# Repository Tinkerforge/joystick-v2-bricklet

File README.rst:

Joystick Bricklet 2.0
=====================

This repository contains the firmware source code and the hardware design
files. The documentation generator configs can be found at
https://github.com/Tinkerforge/generators

Repository Content
------------------

software/:
 * examples/: Examples for all supported languages
 * build/: Compiled files
 * src/: Source code of firmware
 * Makefile: Makefile to build project

hardware/:
 * Contains KiCad project files and additionally schematics as PDF

datasheets/:
 * Contains datasheets for sensors and complex ICs that are used

Hardware
--------

The hardware is designed with the open source EDA Suite KiCad
(http://www.kicad.org). Before you are able to open the files,
you have to install the Tinkerforge kicad-libraries
(https://github.com/Tinkerforge/kicad-libraries). You can either clone
them directly in hardware/ or clone them in a separate folder and
symlink them into hardware/
(ln -s kicad_path/kicad-libraries project_path/hardware). After that you
can open the .pro file in hardware/ with KiCad and from there view and
modify the schematics and the PCB layout.

Software
--------

If you want to do your own Brick/Bricklet firmware development we highly
recommend that you use our build environment setup script and read the
tutorial (https://www.tinkerforge.com/en/doc/Tutorials/Tutorial_Build_Environment/Tutorial.html).

To compile the C code we recommend you to install the newest GNU Arm Embedded
Toolchain (https://launchpad.net/gcc-arm-embedded/+download).
You also need to install bricklib2 (https://github.com/Tinkerforge/bricklib2).

You can either clone it directly in software/src/ or clone it in a
separate folder and symlink it into software/src/
(ln -s bricklib_path/bricklib2 project_path/software/src/). Finally make sure to
have CMake installed (http://www.cmake.org/cmake/resources/software.html).

After that you can build the firmware by invoking make in software/.
The firmware (.zbin) can then be found in software/build/ and uploaded
with brickv (click button "Flashing" on start screen).

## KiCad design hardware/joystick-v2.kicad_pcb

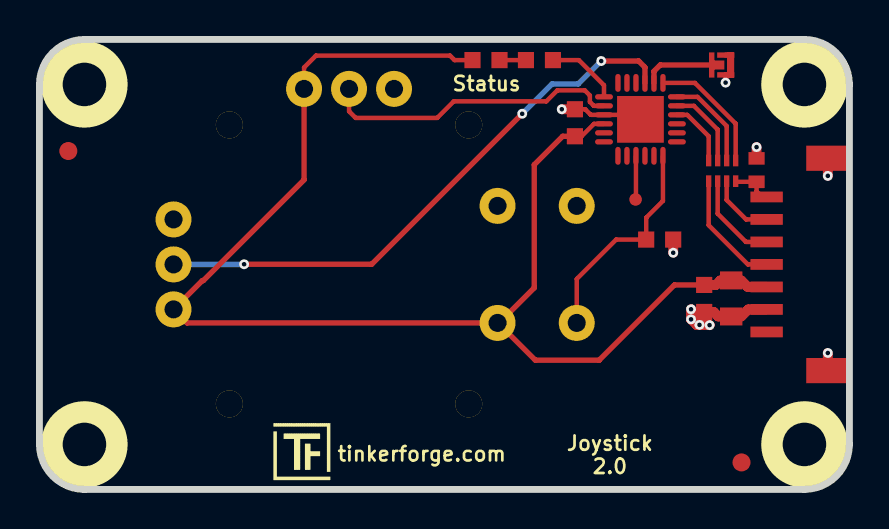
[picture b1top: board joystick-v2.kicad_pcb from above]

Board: 2 copper layers, 45.0 x 25.0 mm, 22 parts (0 on the bottom side), 17 nets.

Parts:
C1: 10uF; C0805
C2: 100nF; C0603F
C3: 220pF; C0402E
C4: 1uF; C0603F
D1: blue; D0603F
Fiducial_Mark: VAL**; Fiducial_Mark
Fiducial_Mark#2: VAL**; Fiducial_Mark
P1: CON-SENSOR2
P2: DEBUG; DEBUG_PAD
P3: BOOT; SolderJumper
R1: 1k; R0603F
R3: 10k; R0603F
RP1: 82; 4X0402
Ref**: Val**; Logo_31x31
U1: XMC1100; QFN24-4x4mm-0.5mm
U3: JOYSTICK_BUTTON; Joystick_Button
U4, U5, U6, U7: DRILL; DRILL_NP
VAL: WEEE_7mm
VAL#2: CE_5mm

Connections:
GND: C1.1, C2.1, C3.1, C4.1, P1.2, P1.EP, P3.1, R3.2, U1.9, U1.EXP, U3.X3, U3.Y3
unnamed: C3.2, P1.7, RP1.4
unnamed: D1.2, R1.2
unnamed: P1.4, RP1.1
unnamed: P1.5, RP1.2
unnamed: P1.6, RP1.3
unnamed: P2.1, U1.15
unnamed: P3.2, U1.2
unnamed: R1.1, U1.7
S-CLK: RP1.7, U1.23
S-CS: RP1.8, U1.22
S-MISO: RP1.5, U1.1
S-MOSI: RP1.6, U1.24
SWITCH: R3.1, U1.18, U3.SW2
VCC: C1.2, C2.2, C4.2, D1.1, P1.3, U1.10, U3.SW1, U3.X1, U3.Y1
X: U1.8, U3.X2
Y: U1.3, U3.Y2

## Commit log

2018-05-18 Add schematic
2018-05-18 Add layout (tbc)
2018-05-28 Add layout
2018-06-28 Fix readme
2018-06-28 Add .gitignore
2018-07-11 Fix origin
2018-07-27 Add auto-generated stub firmware
2018-07-31 Add 3d model (*.FCStd & *.step)
2018-07-31 Add 3d information (final)
2019-01-17 drc check
2019-02-20 Add Joystick Bricklet 2.0 API and implementation
2019-02-20 Implement callback
2019-02-20 Use tabs instead of spaces
2019-02-22 fixed lib, added sym_lib_table, changed processor to XMC1100
2019-03-28 mqtt: Fix whitespace.
2019-03-28 Add examples.
2019-04-30 Turn logging off
2019-05-10 add cutout information
2019-05-15 add 3d data
2019-05-15 add new 3d data
2019-05-20 Update auto-generated rust example
2019-05-20 Release Bricklet
2019-05-20 rust: Use merged imports again.
2019-05-29 Increase version for new release (changes in bricklib2)
2019-05-29 Add rev to changelog
2019-08-22 c: Adapt to bindings changes
2019-09-09 Fix bug in callback handler
2019-09-09 Add ref for 2.0.2
2020-01-13 examples: Use python3 input instead of python2 raw_input.
2020-01-13 examples: mqtt: Remove trailing whitespace.
2020-08-19 Add uc examples.
2020-08-25 uc: Fix whitespace
2020-08-27 uc: Fix warnings.
2020-08-31 uc: Use fixed-with placeholders in format strings.
2020-09-02 uc: Add example driver note.
2021-10-25 Update KiCad link
    https://www.kicad.org/blog/2021/10/Avoid-links-to-former-kicad-domain/
2022-04-19 examples: uc: Rename TF_HalContext to TF_HAL.
2022-04-27 uc: Adapt to bindings changes
2022-05-10 go: Fix format string
2022-07-06 Add license files.
2025-10-04 Fix compatibility with new Docker build image (GCC 14.2.1)

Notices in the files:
hardware/joystick-v2.kicad_pcb:
Licensed under CERN OHL v.1.1
Copyright (©) 2018, L.Lauer
Copyright Tinkerforge GmbH 2018.
This documentation describes Open Hardware and is licensed under the
CERN OHL v. 1.1.
